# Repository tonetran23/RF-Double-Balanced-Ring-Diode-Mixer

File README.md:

This respository inclues a pdf and doc of circuit and simulation results and KiCAD schematic and PCB layout.

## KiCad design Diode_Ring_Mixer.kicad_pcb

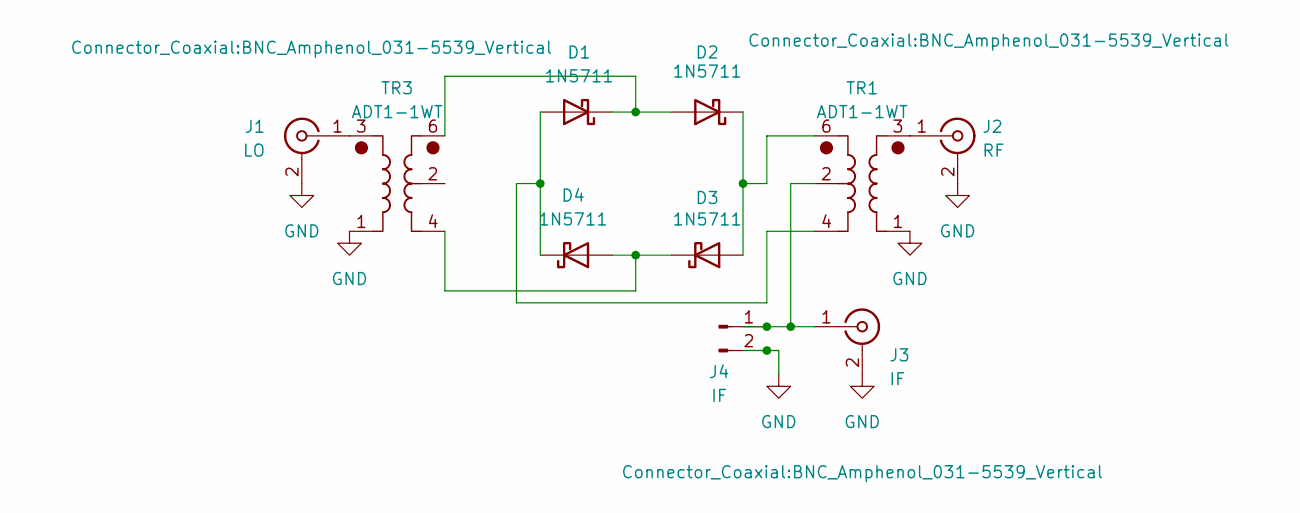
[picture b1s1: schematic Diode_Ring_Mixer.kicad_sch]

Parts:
D1, D2, D3, D4: 1N5711; D_DO-35_SOD27_P7.62mm_Horizontal
J1: LO; BNC_Amphenol_031-5539_Vertical
J2: RF; BNC_Amphenol_031-5539_Vertical
J3: IF; BNC_Amphenol_031-5539_Vertical
J4: IF
TR1, TR3: ADT1-1WT; Mini-Circuits_CD542_H2.84mm

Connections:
GND: J1.2 (Ext), J2.2 (Ext), J3.2 (Ext), J4.2, TR1.1, TR3.1
unnamed: D1.2 (A), D4.1 (K), TR1.4
unnamed: D1.1 (K), D2.2 (A), TR3.6
unnamed: D2.1 (K), D3.2 (A), TR1.6
unnamed: D3.1 (K), D4.2 (A), TR3.4
unnamed: J1.1 (In), TR3.3
unnamed: J2.1 (In), TR1.3
unnamed: J3.1 (In), J4.1, TR1.2

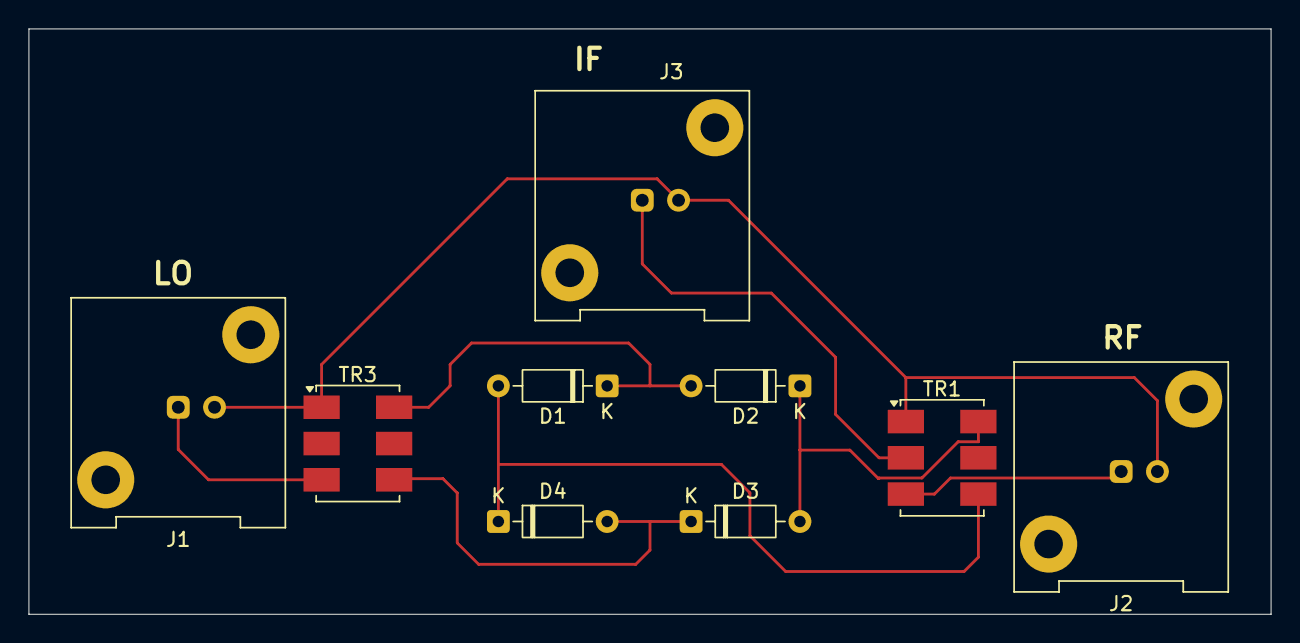
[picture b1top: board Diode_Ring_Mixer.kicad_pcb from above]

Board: 2 copper layers, 87.0 x 41.0 mm, 9 parts (0 on the bottom side), 8 nets.

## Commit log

2026-04-07 Add files via upload
    LTspice simulation results
2026-04-07 Add files via upload
    PCB update. added grounding plate and connection names
2026-04-07 Add files via upload
    LTspice circuit
